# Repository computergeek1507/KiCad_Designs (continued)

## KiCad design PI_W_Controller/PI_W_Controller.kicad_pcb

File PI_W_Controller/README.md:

# Copyright and Disclaimer
Copyright: Scott Hanson

This documentation describes Open Hardware and is licensed under the CERN OHL v. 1.2.

You may redistribute and modify this documentation under the terms of the CERN OHL v.1.2. (http://ohwr.org/cernohl). This documentation is distributed WITHOUT ANY EXPRESS OR IMPLIED WARRANTY, INCLUDING OF MERCHANTABILITY, SATISFACTORY QUALITY AND FITNESS FOR A PARTICULAR PURPOSE. Please see the CERN OHL v.1.2 for applicable conditions

# 8 Port Raspberry PI Zero Controller

8 Port Controller for a Raspberry PI Zero/ Zero W. The design was made with all through hole components for easy assembly by most users. Open source applications were used to create this controller. [KiCad](http://kicad-pcb.org/) was used for the PCB design, and [LibreOffice](https://www.libreoffice.org/) for the documentation.

Developed with KiCad 6.

To order your own PCB upload the gerber.zip file to your favorite PCB manufacture of choice, I personally use [jlcpcb.com](https://jlcpcb.com/).

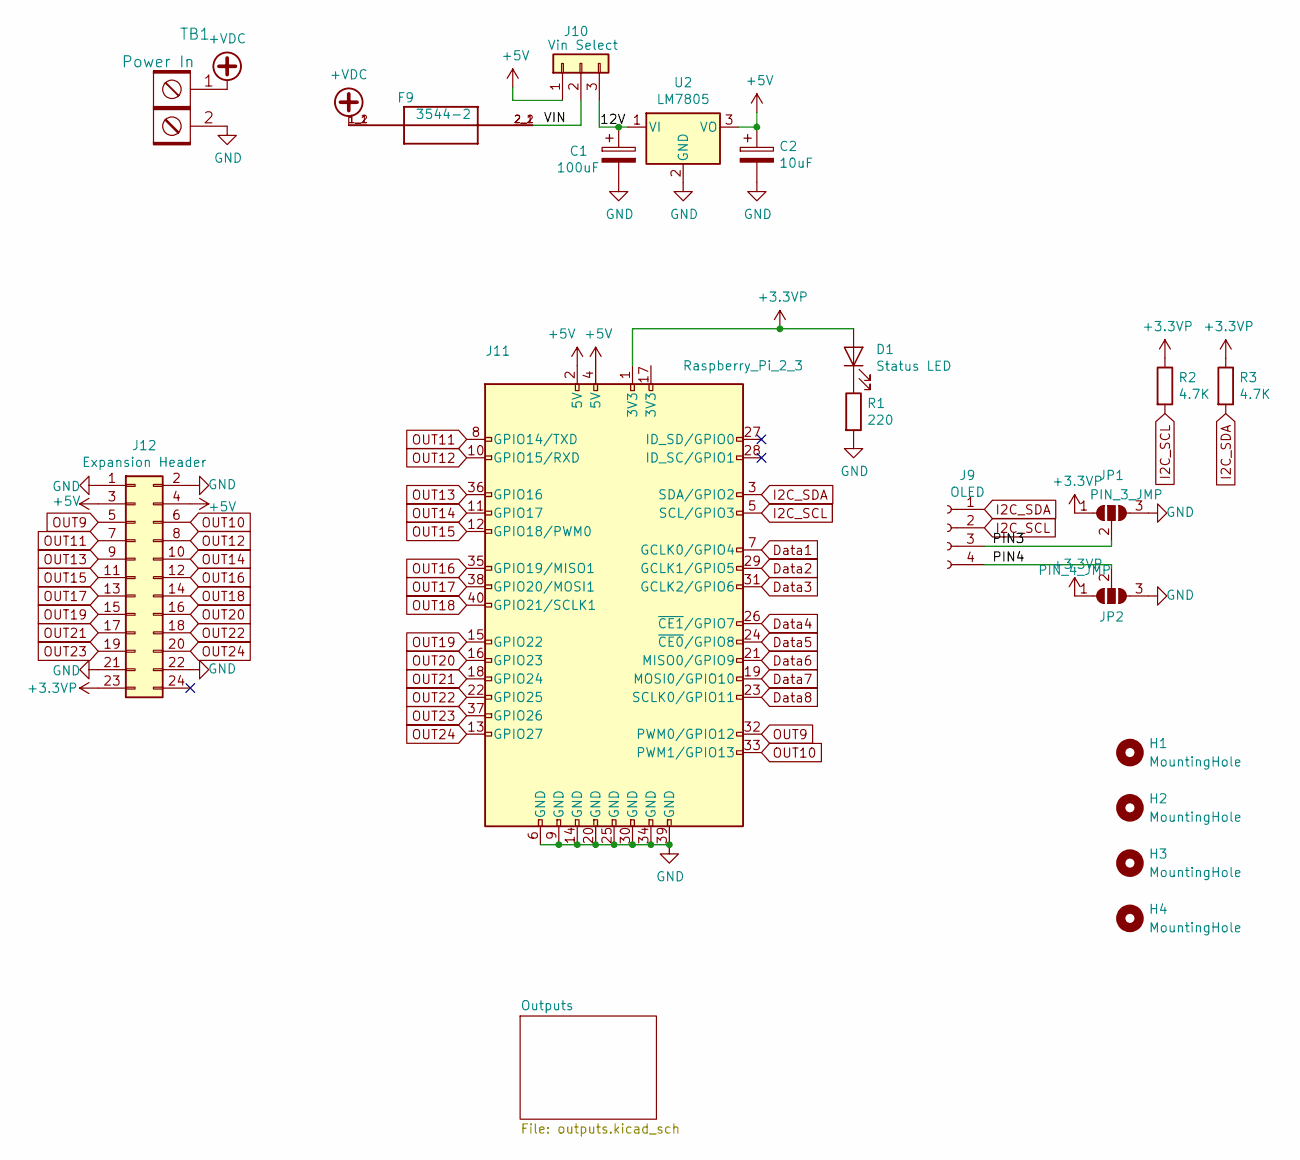
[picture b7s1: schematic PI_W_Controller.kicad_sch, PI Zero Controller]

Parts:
C1: 100uF; CP_Radial_D8.0mm_P3.50mm; MPN UVR1H101MPD; Digi-Key_PN 493-1107-ND
C2: 10uF; CP_Radial_D5.0mm_P2.00mm; MPN ECA-1EM100; Digi-Key_PN P5148-ND
D1: Status LED; LED_D3.0mm; MPN 151031VS06000; Digi-Key_PN 732-5008-ND
F9: 3544-2; FUSE_3544-2; MPN 3544-2; Digi-Key_PN 36-3544-2-ND
H1, H2, H3, H4: MountingHole; MountingHole_3.7mm
J9: OLED; OLED-SSD1306-128X64-I2C-THT; MPN PPTC041LFBN-RC; Digi-Key_PN S7002-ND
J10: Vin Select; PinHeader_1x03_P2.54mm_Vertical
J11: Raspberry_Pi_2_3; Raspberry_Pi_Zero_Socketed_THT_FaceDown_MountingHoles
J12: Expansion Header; OST_302-S241; MPN 302-S241; Digi-Key_PN ED10525-ND
JP1: PIN_3_JMP; SolderJumper-3_P1.3mm_Open_Pad1.0x1.5mm
JP2: PIN_4_JMP; SolderJumper-3_P1.3mm_Open_Pad1.0x1.5mm
R1: 220; R_Axial_DIN0207_L6.3mm_D2.5mm_P7.62mm_Horizontal; MPN CF14JT56R0; Digi-Key_PN CF14JT56R0CT-ND
R2, R3: 4.7K; R_Axial_DIN0207_L6.3mm_D2.5mm_P7.62mm_Horizontal
TB1: Power In; BARRIER_BLOCK_1ROW_2POS_P9.5MM
U2: LM7805; 1.5-W36-C; MPN LM7805CT; Digi-Key_PN 296-47192-ND

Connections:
+3.3VP: D1.2 (A), J11.1 (3V3), J12.23, JP1.1 (A), JP2.1 (A), R2.1, R3.1
+5V: C2.1, J10.1, J11.2 (5V), J11.4 (5V), J12.3, J12.4, U2.3 (VO); also elsewhere on the board
+VDC: F9.1_1 (1), F9.1_2 (1), TB1.1; also elsewhere on the board
/12V: C1.1, J10.3, U2.1 (VI)
/PIN3: J9.3, JP1.2 (C)
/PIN4: J9.4, JP2.2 (C)
/VIN: F9.2_1 (2), F9.2_2 (2), J10.2
Data1: J11.7 (GCLK0/GPIO4); also elsewhere on the board
Data2: J11.29 (GCLK1/GPIO5); also elsewhere on the board
Data3: J11.31 (GCLK2/GPIO6); also elsewhere on the board
Data4: J11.26 (~CE1/GPIO7); also elsewhere on the board
Data5: J11.24 (~CE0/GPIO8); also elsewhere on the board
Data6: J11.21 (MISO0/GPIO9); also elsewhere on the board
Data7: J11.19 (MOSI0/GPIO10); also elsewhere on the board
Data8: J11.23 (SCLK0/GPIO11); also elsewhere on the board
GND: C1.2, C2.2, J11.6 (GND), J11.9 (GND), J11.14 (GND), J11.20 (GND), J11.25 (GND), J11.30 (GND), J11.34 (GND), J11.39 (GND), J12.1, J12.2, J12.21, J12.22, JP1.3 (B), JP2.3 (B), R1.2, TB1.2, U2.2 (GND); also elsewhere on the board
I2C_SCL: J9.2, J11.5 (SCL/GPIO3), R2.2
I2C_SDA: J9.1, J11.3 (SDA/GPIO2), R3.2
unnamed: D1.1 (K), R1.1
OUT9: J11.32 (PWM0/GPIO12), J12.5
OUT10: J11.33 (PWM1/GPIO13), J12.6
OUT11: J11.8 (GPIO14/TXD), J12.7
OUT12: J11.10 (GPIO15/RXD), J12.8
OUT13: J11.36 (GPIO16), J12.9
OUT14: J11.11 (GPIO17), J12.10
OUT15: J11.12 (GPIO18/PWM0), J12.11
OUT16: J11.35 (GPIO19/MISO1), J12.12
OUT17: J11.38 (GPIO20/MOSI1), J12.13
OUT18: J11.40 (GPIO21/SCLK1), J12.14
OUT19: J11.15 (GPIO22), J12.15
OUT20: J11.16 (GPIO23), J12.16
OUT21: J11.18 (GPIO24), J12.17
OUT22: J11.22 (GPIO25), J12.18
OUT23: J11.37 (GPIO26), J12.19
OUT24: J11.13 (GPIO27), J12.20

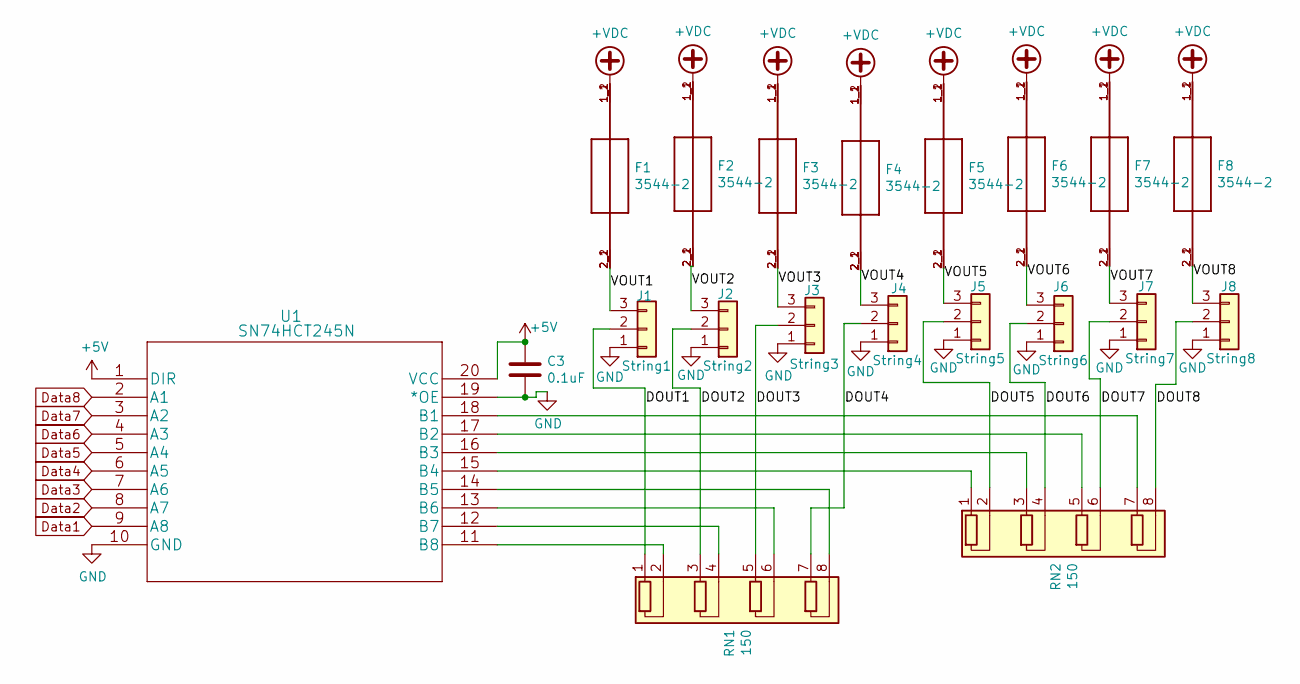
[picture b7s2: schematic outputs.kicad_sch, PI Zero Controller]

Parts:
C3: 0.1uF; C_Rect_L7.0mm_W2.0mm_P5.00mm; MPN SR215C104KARTR1; Digi-Key_PN 478-7336-1-ND
F1, F2, F3, F4, F5, F6, F7, F8: 3544-2; FUSE_3544-2; MPN 3544-2; Digi-Key_PN 36-3544-2-ND
J1: String1; PhoenixContact_MCV_1,5_3-G-3.5_1x03_P3.50mm_Vertical; MPN 1843619/OSTTJ0311530; Digi-Key_PN 277-5737-ND/ED10555-ND
J2: String2; PhoenixContact_MCV_1,5_3-G-3.5_1x03_P3.50mm_Vertical; MPN 1843619/OSTTJ0311530; Digi-Key_PN 277-5737-ND/ED10555-ND
J3: String3; PhoenixContact_MCV_1,5_3-G-3.5_1x03_P3.50mm_Vertical; MPN 1843619/OSTTJ0311530; Digi-Key_PN 277-5737-ND/ED10555-ND
J4: String4; PhoenixContact_MCV_1,5_3-G-3.5_1x03_P3.50mm_Vertical; MPN 1843619/OSTTJ0311530; Digi-Key_PN 277-5737-ND/ED10555-ND
J5: String5; PhoenixContact_MCV_1,5_3-G-3.5_1x03_P3.50mm_Vertical; MPN 1843619/OSTTJ0311530; Digi-Key_PN 277-5737-ND/ED10555-ND
J6: String6; PhoenixContact_MCV_1,5_3-G-3.5_1x03_P3.50mm_Vertical; MPN 1843619/OSTTJ0311530; Digi-Key_PN 277-5737-ND/ED10555-ND
J7: String7; PhoenixContact_MCV_1,5_3-G-3.5_1x03_P3.50mm_Vertical; MPN 1843619/OSTTJ0311530; Digi-Key_PN 277-5737-ND/ED10555-ND
J8: String8; PhoenixContact_MCV_1,5_3-G-3.5_1x03_P3.50mm_Vertical; MPN 1843619/OSTTJ0311530; Digi-Key_PN 277-5737-ND/ED10555-ND
RN1, RN2: 150; R_Array_SIP8; MPN 4608X-102-151LF; Digi-Key_PN 4608X-2-151LF-ND
U1: SN74HCT245N; MPN SN74HCT245N; Digi-Key_PN 296-1612-5-ND

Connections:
+5V: C3.1, U1.1 (DIR), U1.20 (VCC); also elsewhere on the board
+VDC: F1.1_1 (1), F1.1_2 (1), F2.1_1 (1), F2.1_2 (1), F3.1_1 (1), F3.1_2 (1), F4.1_1 (1), F4.1_2 (1), F5.1_1 (1), F5.1_2 (1), F6.1_1 (1), F6.1_2 (1), F7.1_1 (1), F7.1_2 (1), F8.1_1 (1), F8.1_2 (1); also elsewhere on the board
/Outputs/DOUT1: J1.2, RN1.1 (R1.1)
/Outputs/DOUT2: J2.2, RN1.3 (R2.1)
/Outputs/DOUT3: J3.2, RN1.5 (R3.1)
/Outputs/DOUT4: J4.2, RN1.7 (R4.1)
/Outputs/DOUT5: J5.2, RN2.2 (R1.2)
/Outputs/DOUT6: J6.2, RN2.4 (R2.2)
/Outputs/DOUT7: J7.2, RN2.6 (R3.2)
/Outputs/DOUT8: J8.2, RN2.8 (R4.2)
/Outputs/VOUT1: F1.2_1 (2), F1.2_2 (2), J1.3
/Outputs/VOUT2: F2.2_1 (2), F2.2_2 (2), J2.3
/Outputs/VOUT3: F3.2_1 (2), F3.2_2 (2), J3.3
/Outputs/VOUT4: F4.2_1 (2), F4.2_2 (2), J4.3
/Outputs/VOUT5: F5.2_1 (2), F5.2_2 (2), J5.3
/Outputs/VOUT6: F6.2_1 (2), F6.2_2 (2), J6.3
/Outputs/VOUT7: F7.2_1 (2), F7.2_2 (2), J7.3
/Outputs/VOUT8: F8.2_1 (2), F8.2_2 (2), J8.3
Data1: U1.9 (A8); also elsewhere on the board
Data2: U1.8 (A7); also elsewhere on the board
Data3: U1.7 (A6); also elsewhere on the board
Data4: U1.6 (A5); also elsewhere on the board
Data5: U1.5 (A4); also elsewhere on the board
Data6: U1.4 (A3); also elsewhere on the board
Data7: U1.3 (A2); also elsewhere on the board
Data8: U1.2 (A1); also elsewhere on the board
GND: C3.2, J1.1, J2.1, J3.1, J4.1, J5.1, J6.1, J7.1, J8.1, U1.10 (GND), U1.19 (*OE); also elsewhere on the board
unnamed: RN1.2 (R1.2), U1.11 (B8)
unnamed: RN1.4 (R2.2), U1.12 (B7)
unnamed: RN1.6 (R3.2), U1.13 (B6)
unnamed: RN1.8 (R4.2), U1.14 (B5)
unnamed: RN2.1 (R1.1), U1.15 (B4)
unnamed: RN2.3 (R2.1), U1.16 (B3)
unnamed: RN2.5 (R3.1), U1.17 (B2)
unnamed: RN2.7 (R4.1), U1.18 (B1)

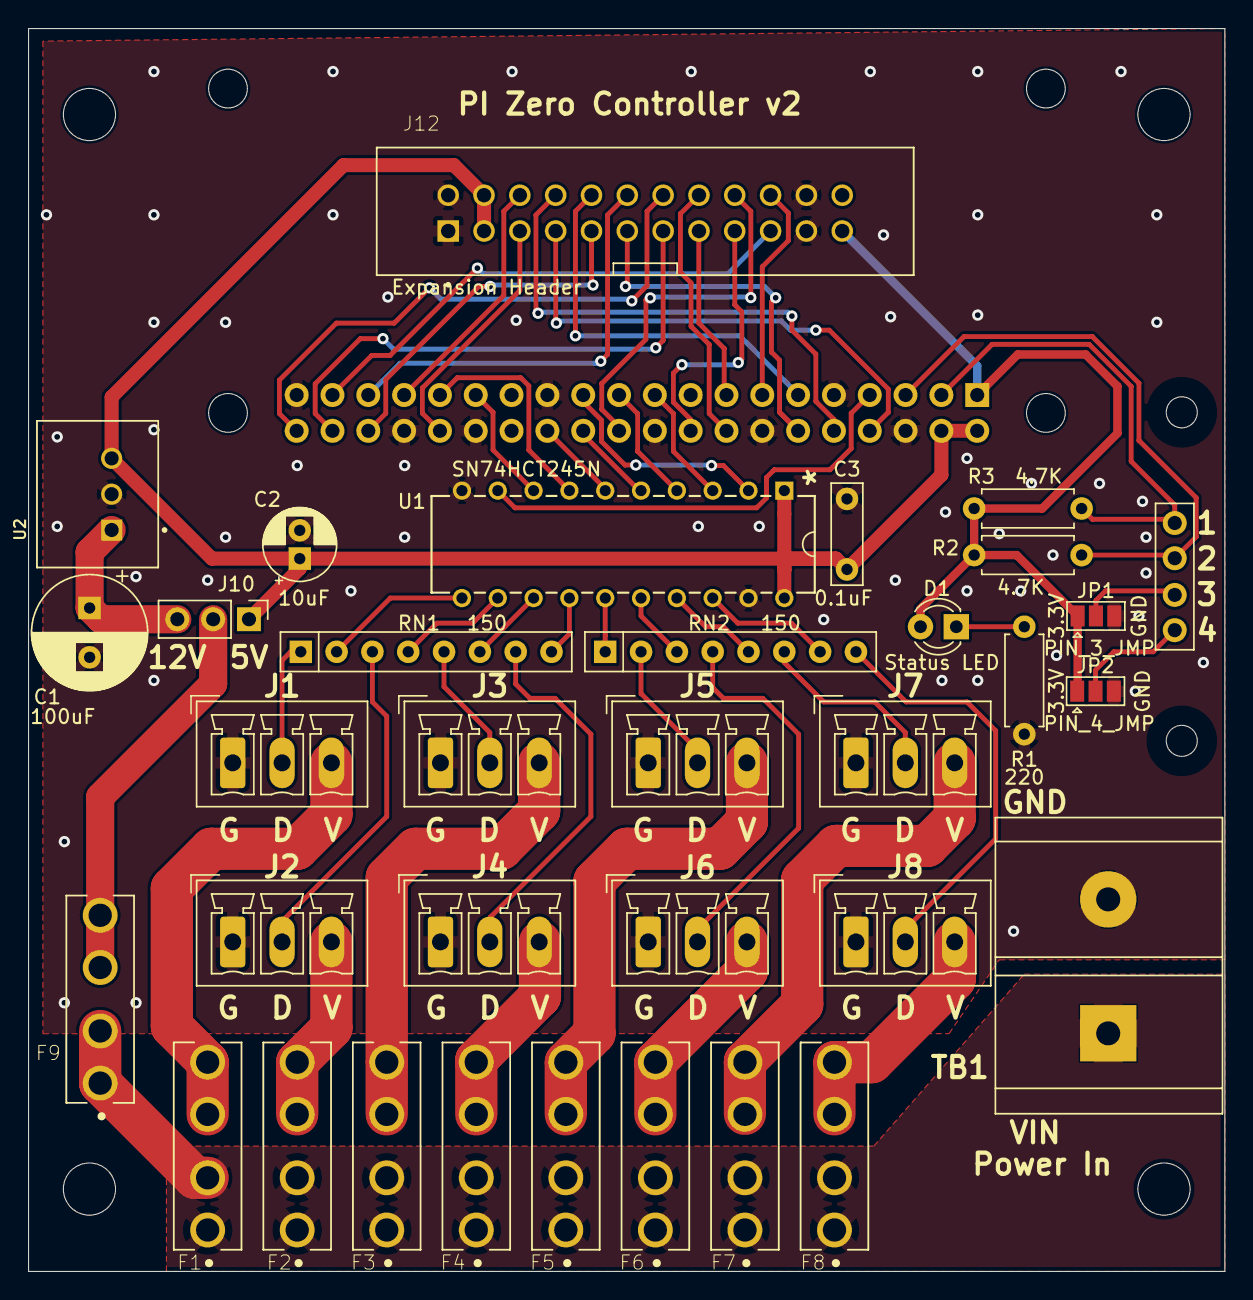
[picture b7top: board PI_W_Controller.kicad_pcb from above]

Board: 2 copper layers, 84.8 x 88.1 mm, 39 parts (1 on the bottom side), 59 nets.

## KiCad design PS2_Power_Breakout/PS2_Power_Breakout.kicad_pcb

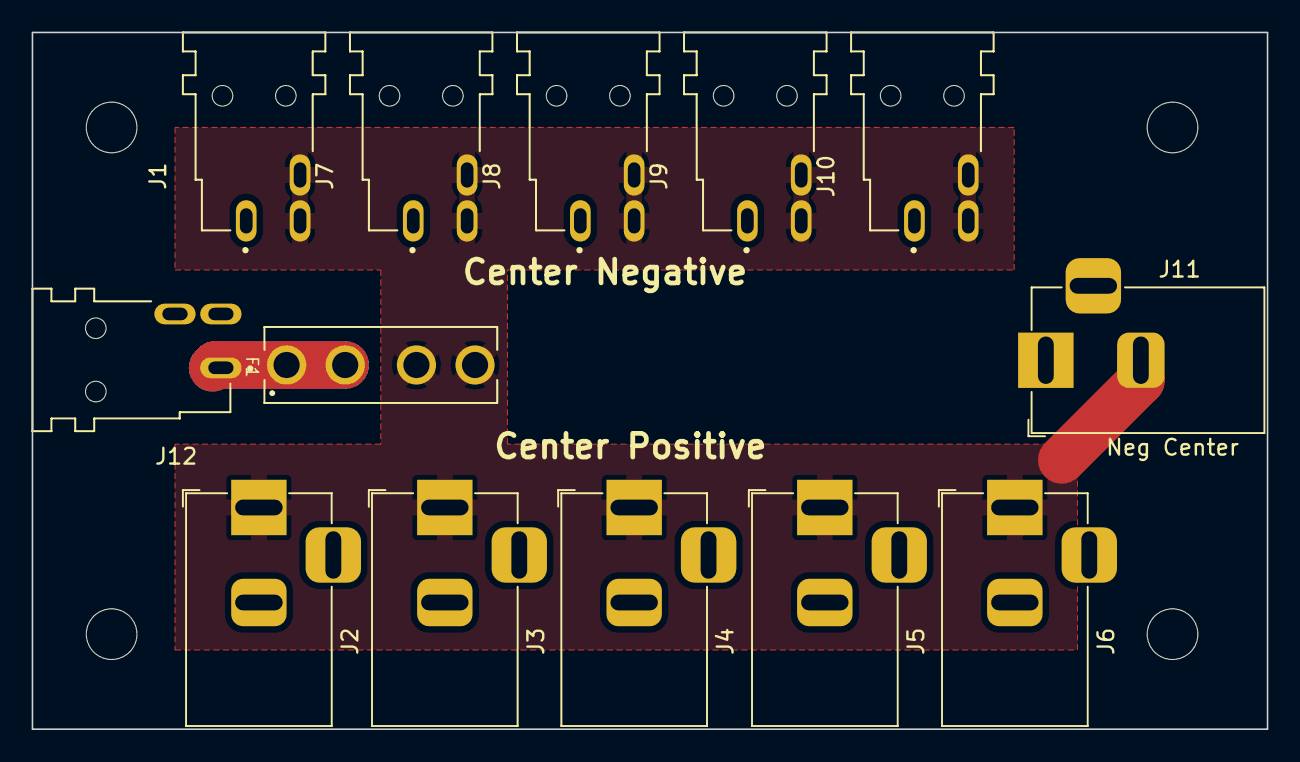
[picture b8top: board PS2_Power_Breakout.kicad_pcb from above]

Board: 2 copper layers, 78.0 x 44.0 mm, 17 parts (0 on the bottom side), 3 nets.

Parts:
F1: 3544-2; FUSE_3544-2
H1, H2, H3, H4: MountingHole; MountingHole_3.2mm_M3
J1, J7, J8, J9, J10, J12: PJ-041H; CUI_PJ-041H
J2, J3, J4, J5, J6: Pos Center; BarrelJack_Horizontal
J11: Neg Center; BarrelJack_Horizontal

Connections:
/VIN: F1.1_1 (1), F1.1_2 (1), J12.1
GND: J1.1, J2.2, J3.2, J4.2, J5.2, J6.2, J7.1, J8.1, J9.1, J10.1, J11.1, J12.2, J12.3
VCC: F1.2_1 (2), F1.2_2 (2), J1.2, J1.3, J2.1, J3.1, J4.1, J5.1, J6.1, J7.2, J7.3, J8.2, J8.3, J9.2, J9.3, J10.2, J10.3, J11.2
